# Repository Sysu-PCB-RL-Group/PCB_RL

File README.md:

# PCB_RL

基于强化学习的 PCB 自动布局（Double DQN）。

> ⚠️ 本项目 **2026-09-22 起整体重构**：旧的 5 步动作栈（`env/pcb_layout_env.py` +
> `dqn/` + `config/argument.txt` + `main.py/run.py/run_inference.py` 那套）**已废弃并删除**。
> 本文以下内容全部是现行架构。

## 先读这三份

- **技术总览（新人从这里开始，约 300 行）**：[`docs/项目技术文档.md`](docs/项目技术文档.md)
- **当前参数一览（现在到底配的是什么）**：[`PARAMS.md`](PARAMS.md)
- **设计台账（唯一事实来源，2400+ 行，含每个数字的由来）**：[`docs/导入信息重构.md`](docs/导入信息重构.md)

（重构前的旧文档在 `docs/旧版结构文档/`，**已作废**，仅作历史对照。）

## 环境要求

| 项 | 要求 | 说明 |
|---|---|---|
| Python | **3.11** | 项目既有环境即 3.11（conda 环境名 `pcb_rl_311`）；更低版本未验证 |
| 第三方依赖 | 只有 5 个 | `numpy` / `matplotlib` / `gymnasium` / `torch` / `pytest`，见 `requirements.txt`（实测全仓库只 import 这 5 个） |
| KiCad | **训练/推理都不需要** | 只有「重建缓存」和「读真实板的测试」需要 KiCad 10.0+，见下文 |
| 图形显示 | **不需要** | 3 个绘图模块都强制了 `matplotlib.use("Agg")`，没有 `DISPLAY` 也能出图 |
| 网络 | 只有装依赖时需要 | 能访问 PyPI（或内网镜像）即可；依赖装完后训练/推理全程离线 |
| 磁盘 | 约 62 MB | 其中 `data/` 约 62 MB（板源文件 + 离线缓存） |

## 安装（新机器 / Linux 服务器）

```bash
git clone https://github.com/Sysu-PCB-RL-Group/PCB_RL.git
cd PCB_RL

# ① conda（推荐，与本机环境同名同版本）
conda create -n pcb_rl_311 python=3.11 -y
conda activate pcb_rl_311
# ② 或者 venv
#   python3 -m venv .venv && source .venv/bin/activate

python -m pip install --upgrade pip
python -m pip install torch --index-url https://download.pytorch.org/whl/cpu
python -m pip install -r requirements.txt

# 自检：这行必须打印出版本号，否则说明解释器或依赖没装对
python -c "import torch, numpy, gymnasium, matplotlib; print(torch.__version__, numpy.__version__)"
```

想用 GPU：把 torch 那一行换成

```bash
python -m pip install torch --index-url https://download.pytorch.org/whl/cu124
```

训练时再加 `--device cuda`（**默认是 `cpu`**）。

## 最快跑起来

```bash
python main.py train        # 训练：默认 1000 局 → output/
python main.py infer        # 推理：读 output/best.pt → result/
python main.py help         # 用法
python main.py train --help # 训练的全部参数

# 冒烟（几分钟）：装完环境先跑这个，确认跑得通再上正式训练
python main.py train --episodes 5 --eval-every-episodes 5 --log-every 1 --out output_smoke

python -m pytest tests -q   # 测试（需要 KiCad 的用例会自动 skip）
```

`main.py train|infer` 的参数**原样透传**给 `scripts/train_dqn.py` /
`scripts/infer_dqn.py`，所以用 `--help` 看全部选项。

Windows 本机等价写法（本机 conda 环境的绝对路径）：

```powershell
cd E:\PCB_AI\PCB_RL
& E:\miniconda\envs\pcb_rl_311\python.exe main.py train
```

## 常用参数

默认值来自 `scripts/train_dqn.py`：

| 参数 | 默认值 | 用途 |
|---|---|---|
| `--episodes` | `1000` | 训练局数（冒烟用 `5`） |
| `--device` | `cpu` | `cpu` / `cuda` |
| `--threads` | `0` | torch CPU 线程数；`0` = 用默认（吃满核，多人共用机器时建议显式限制） |
| `--out` | `output` | 产物目录（**训练开始时会先清空该目录**，见下） |
| `--boards` | 全部 | 逗号分隔的板名，只跑其中几块 |
| `--seed` | `114514` | 随机种子，固定（连网络初始化都由它决定） |
| `--eval-every-episodes` | `50` | 每多少局评估一次（评估更优就写 `best.pt`） |

## 输入数据与产物

- **输入**：`data/model_cache/` —— 16 块板的离线几何缓存（`index.json` + 16 个
  `.pkl`，共 17 个文件、约 1.1 MB，**随仓库一起 clone 下来**）。这是训练/推理
  **唯一**的几何来源：**不要删、也不要重新生成**（重新生成需要 KiCad）。
- **产物**：`output/`（`best.pt` / `train_curves.png` / `train.log` / `log.jsonl`）、
  `result/`。这两类目录都在 `.gitignore` 里，不会污染仓库。
- ⚠️ **`--out` 指向的目录会在训练开始时被清空**。代码里有安全闸：目标目录若含
  `.git` / `data` / `env` / `tests` / `scripts` / `docs` / `utils` 之一（或就是仓库
  根目录）会直接报错拒绝执行 —— 但别去试。

## 关于 KiCad

训练与推理**不需要 KiCad**：`env/` 里 0 处调用 `pcbnew`（只在一条注释里提到），
几何全部从 `data/model_cache/` 读。只有下面两件事需要本机装 KiCad **10.0+**
并设置 `KICAD_PATH`：

1. 重建模型缓存：`python scripts/dump_models.py`
2. 读真实板的测试：`pytest tests/kicad`

没装 KiCad 时，`pytest tests` 里需要 KiCad 的用例会**自动跳过**，其余照常运行。

下载：<https://www.kicad.org/download/>

## 训练要多久 / 怎么盯进度

默认 1000 局（16 块板），**本机 CPU 实测参考约 4.4 小时**。训练过程中每 10 局往
`output/train.log` 打一行进度、每 50 局打一行评估；日志每局都落盘，可以随时

```bash
tail -f output/train.log
```

看进度。

## 排障

| 症状 | 原因 / 处理 |
|---|---|
| `main.py` 提示"这个解释器没有 torch" | 用错解释器了：必须用装了依赖的那个（见「安装」） |
| `CacheError: 缓存索引不存在：…` | `data/model_cache/index.json` 缺失 —— 从仓库重新 clone，别删缓存 |
| `CacheVersionError` | 缓存版本与代码不匹配：代码改过 `PcbModel` 字段，需要重新 dump（要有 KiCad） |
| 训练一开始就报"拒绝清零 …" | `--out` 指到了仓库目录，换成 `output` 之类的独立目录 |
| 出图里的中文显示成方框 | 运行环境缺中文字体。仓库里有 `setup_chinese_font` 做回退（`utils/viz_layout.py`），但**未在没装字体的 Linux 上验证过**；只影响图面文字，不影响数值与训练结果 |

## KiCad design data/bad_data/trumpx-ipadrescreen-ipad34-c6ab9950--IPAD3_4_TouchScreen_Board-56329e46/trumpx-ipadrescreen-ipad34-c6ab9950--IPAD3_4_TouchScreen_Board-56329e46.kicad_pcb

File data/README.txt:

此目录存放 PCB RL 项目的训练/推理数据与生成产物。

## 目录结构
- kicad-native-batch/   立创 EDA 导出的真实 KiCad 项目（.kicad_pcb），供训练循环扫描。
                        env/pcb_layout_env.py 的 get_all_files() 会递归扫描此目录。
- expert_transitions/   专家轨迹生成产物：
                          * <board>_expert.json     量化后的 transition 缓存（训练注入用）
                          * <board>_expert_raw.json  raw 轨迹缓存（含 shift / base / 变异类型 /
                                                    拆分前完整 reward，供 analyze_expert.py 审查）
- README.txt / .gitkeep 本说明与空目录占位文件。

## 当前状态（2026-08-24）
- 唯一训练板：开关小板
  （ran-pang-airlink-86231b34--开关小板-883285b3，FP=6, Net=3, grid 36×36）。
- 自 2026-08-01 起统一使用真实 KiCad 数据，不再用 env/mock_pcb.py 合成数据。
- 专家轨迹生成：python generate_expert_only.py --board 开关小板
- 轨迹质量审查：python analyze_expert.py --board airlink

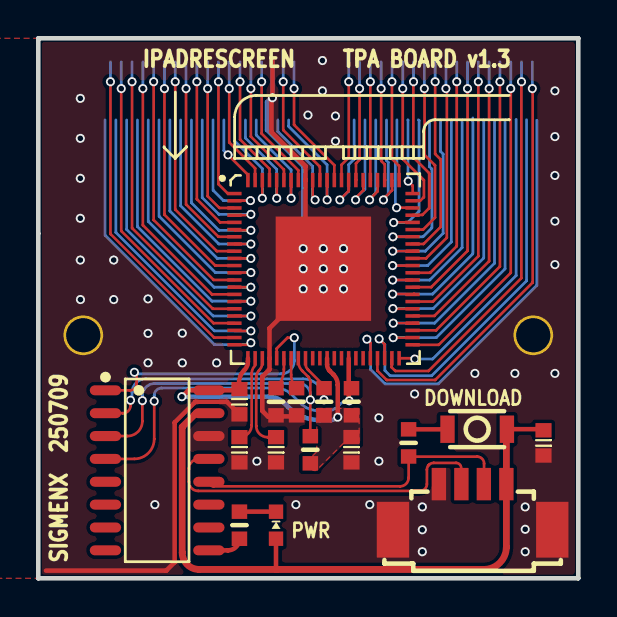
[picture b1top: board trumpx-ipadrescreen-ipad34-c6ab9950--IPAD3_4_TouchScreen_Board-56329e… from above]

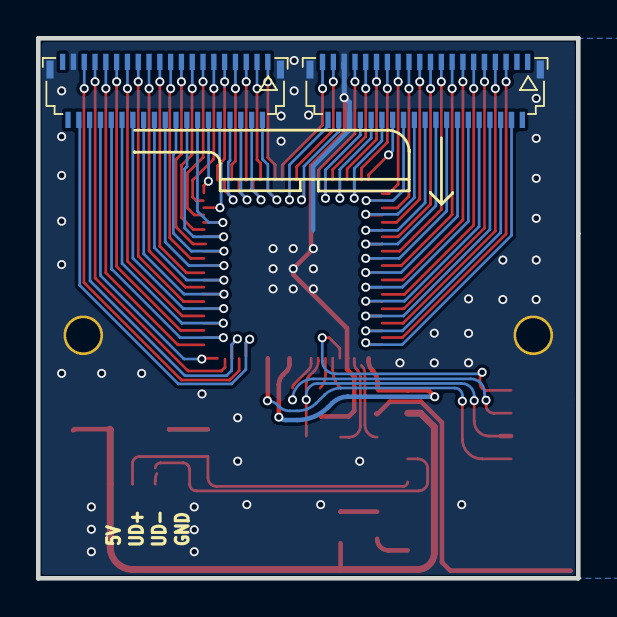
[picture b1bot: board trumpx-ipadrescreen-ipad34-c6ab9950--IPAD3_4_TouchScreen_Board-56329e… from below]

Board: 2 copper layers, 30.0 x 30.0 mm, 19 parts (2 on the bottom side), 86 nets.

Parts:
C1, C2, C3, C5, C6: c0603_neo
FPC2: CONN-SMD_1.25-4PWB
LED1: LED0603
R1, R2, R3, R4, R5, R6, R7: r0603_neo
U1: GT9110
U2, U3: CONN-SMD_FH26-39S-0.3SHW
U4: SW-SMD_L3.0-W2.0-LS3.5
U5: SOP-16_L10.0-W3.9-P1.27-LS6.0-BL

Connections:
$1N6411: C2.2, U1.24
$1N6412: C3.2, U1.25
$1N6447: R1.2, U4.1
$1N6516: R7.2, U5.9
$1N6523: LED1.2, R7.1
+5V: C5.2, FPC2.4, LED1.1, U4.2, U5.15
GND: C1.1, C2.1, C3.1, C5.1, C6.1, FPC2.1, FPC2.5, FPC2.6, R5.2, R6.2, U1.26, U1.80, U1.89, U2.37, U2.40, U2.41, U3.34, U3.35, U3.40, U3.41, U5.14
INT: U1.27, U5.1
MT_IN0: U1.22, U3.4
MT_IN1: U1.21, U3.5
MT_IN2: U1.20, U3.6
MT_IN3: U1.19, U3.7
MT_IN4: U1.18, U3.8
MT_IN5: U1.17, U3.9
MT_IN6: U1.16, U3.10
MT_IN7: U1.15, U3.11
MT_IN8: U1.14, U3.12
MT_IN9: U1.13, U3.13
MT_IN10: U1.12, U3.14
MT_IN11: U1.11, U3.15
MT_IN12: U1.10, U3.16
MT_IN13: U1.9, U3.17
MT_IN14: U1.8, U3.18
MT_IN15: U1.7, U3.19
MT_IN16: U1.6, U3.20
MT_IN17: U1.5, U3.21
MT_IN18: U1.4, U3.22
MT_IN19: U1.3, U3.23
MT_IN20: U1.2, U3.24
MT_IN21: U1.1, U3.25
MT_IN22: U1.88, U3.26
MT_IN23: U1.87, U3.27
MT_IN24: U1.86, U3.28
MT_IN25: U1.85, U3.29
MT_IN26: U1.84, U3.30
MT_IN27: U1.83, U3.31
MT_IN28: U1.82, U3.32
MT_IN29: U1.81, U3.33
MT_OUT0: U1.40, U2.36
MT_OUT1: U1.41, U2.35
MT_OUT2: U1.42, U2.34
MT_OUT3: U1.43, U2.33
MT_OUT4: U1.44, U2.32
MT_OUT5: U1.45, U2.31
MT_OUT6: U1.46, U2.30
MT_OUT7: U1.47, U2.29
MT_OUT8: U1.48, U2.28
MT_OUT9: U1.49, U2.27
MT_OUT10: U1.50, U2.26
MT_OUT11: U1.51, U2.25
MT_OUT12: U1.52, U2.24
MT_OUT13: U1.53, U2.23
MT_OUT14: U1.54, U2.22
MT_OUT15: U1.55, U2.21
MT_OUT16: U1.56, U2.20
MT_OUT17: U1.57, U2.19
MT_OUT18: U1.58, U2.18
MT_OUT19: U1.59, U2.17
MT_OUT20: U1.60, U2.16
MT_OUT21: U1.61, U2.15
MT_OUT22: U1.62, U2.14
MT_OUT23: U1.63, U2.13
MT_OUT24: U1.66, U2.12
MT_OUT25: U1.65, U2.11
MT_OUT26: U1.64, U2.10
MT_OUT27: U1.67, U2.9
MT_OUT28: U1.68, U2.8
MT_OUT29: U1.69, U2.7
MT_OUT30: U1.70, U2.6
MT_OUT31: U1.71, U2.5
MT_OUT32: U1.72, U2.4
MT_OUT33: U1.73, U2.3
MT_OUT34: U1.74, U2.2
MT_OUT35: U1.75, U2.1
MT_OUT36: U1.76, U3.39
MT_OUT37: U1.77, U3.38
MT_OUT38: U1.78, U3.37
MT_OUT39: U1.79, U3.36
OPT1: R5.1, U1.28
OPT2: R6.1, U1.29
RST-TS: R4.2, U1.37, U5.4
SCL: R3.1, U1.31, U5.2
SDA: R2.1, U1.30, U5.3
UD+: FPC2.3, R1.1, U5.12
UD-: FPC2.2, U5.13
VDD33: C1.2, C6.2, R2.2, R3.2, R4.1, U1.23, U1.34, U5.16

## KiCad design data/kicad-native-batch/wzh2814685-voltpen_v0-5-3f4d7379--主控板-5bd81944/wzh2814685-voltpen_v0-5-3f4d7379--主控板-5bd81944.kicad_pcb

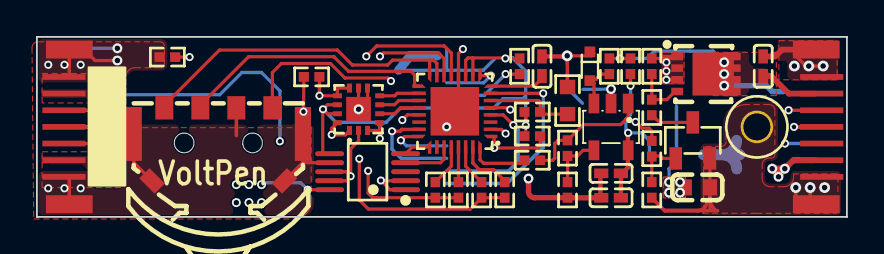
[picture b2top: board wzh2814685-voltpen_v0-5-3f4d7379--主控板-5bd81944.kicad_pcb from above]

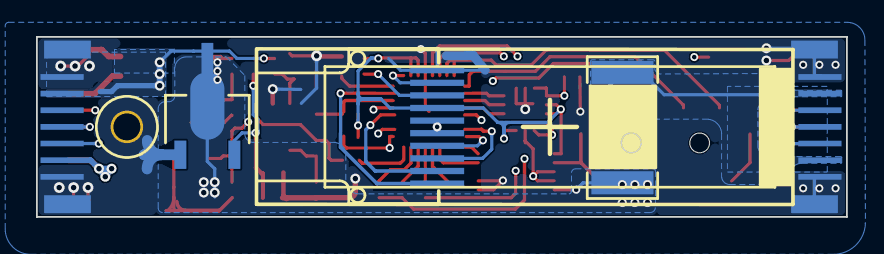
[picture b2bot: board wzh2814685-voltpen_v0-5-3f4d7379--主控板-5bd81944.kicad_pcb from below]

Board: 4 copper layers, 45.0 x 10.0 mm, 37 parts (3 on the bottom side), 39 nets.

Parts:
C1: C0603
C2, C3, C4, C5: C0402
D1: SOD-523_L1.2-W0.8-LS1.6-FD
Q1: WDFN-8_L3.3-W3.3-P0.65-BL
Q2: SOT-23-3_L2.9-W1.3-P1.90-LS2.4-BR
R1, R2, R3, R4, R5, R6, R7, R8, R9, R10, R11, R12, R13, R14, R15, R16, R17, R18: R0402
R19: R2512
RT1: R0603
SW1: SW-SMD_TM-2023-1
TFT-1: 0.99寸-GC9D01N
U1: QFN-32_L4.0-W4.0-P0.40-TL-EP2.7-1
U2: SOT-23-5_L3.0-W1.7-P0.95-LS2.8-BR
U3: MLP-14_L2.5-W2.5-P0.50-BL-EP
U4: MSOP-10_L3.0-W3.0-P0.50-LS5.0-BL
U5: SOT-89-3_L4.5-W2.5-P1.50-LS4.2-BR
USB1, USB2: TYPE-C 14P母座

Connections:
3.3V: C2.1, C4.2, R1.2, R2.2, R10.1, R15.2, TFT-1.7, U1.10, U1.11, U2.5, U3.3, U3.4, U3.12, U3.13, U4.6, U5.3
$1N32: R2.1, TFT-1.8
$1N39: C3.2, U1.8
$1N64: R5.2, R6.1, U2.1
$1N65: R4.2, R5.1, U2.4
$1N66: D1.2, R3.2, U2.3
$1N74: Q2.1, R7.2, R16.2
$1N893: Q2.3, R8.1
$1N902: Q1.4, R8.2, R9.2
ADCN: R1.1, RT1.1, U1.6
ADC_IRON: R6.2, U1.32
BK: TFT-1.9, U1.9
CC1: R17.1, U3.10, U3.11, USB1.A5
CC2: R18.1, U3.1, U3.14, USB1.B5
D+: R13.1, R14.2, U1.14, USB1.A6, USB1.B6
D-: R11.1, R12.2, U1.13, USB1.A7, USB1.B7
D/C: TFT-1.3, U1.23
DD+: R14.1, U1.29
DD-: R12.1, U1.30
GND: C1.2, C2.2, C3.1, C4.1, C5.1, D1.1, Q2.2, R4.1, R16.1, R17.2, R18.2, RT1.2, SW1.3, SW1.4, SW1.5, SW1.6, SW1.C, TFT-1.5, TFT-1.6, TFT-1.10, U1.12, U1.33, U2.2, U3.8, U3.9, U3.15, U4.1, U4.2, U4.7, U5.1, USB1.A1, USB1.A12, USB1.B1, USB1.B12, USB1.SH, USB2.A1, USB2.A12, USB2.B1, USB2.B12, USB2.SH
H_ID: R15.1, U1.1, USB2.A6, USB2.B6
INT302: U1.20, U3.5
K1: SW1.T, U1.17
K2: SW1.2, U1.15, U1.16
K3: SW1.1, U1.21
PWM: R7.1, U1.5
RES: TFT-1.4, U1.24
SCL: TFT-1.2, U1.4
SCL226: U1.25, U4.5
SCL302: U1.19, U3.6
SDA: TFT-1.1, U1.7
SDA226: U1.27, U4.4
SDA302: U1.18, U3.7
SLP: U1.2, USB2.A7, USB2.B7
TEMP: C5.2, Q1.5, R3.1, R10.2, USB2.A4, USB2.A9, USB2.B4, USB2.B9
UD+: R13.2, U1.28
UD-: R11.2, U1.31
VBUS: C1.1, Q1.1, Q1.2, Q1.3, R9.1, R19.2, U4.10, U5.2
VBUS_I: R19.1, U3.2, U4.8, U4.9, USB1.A4, USB1.A9, USB1.B4, USB1.B9

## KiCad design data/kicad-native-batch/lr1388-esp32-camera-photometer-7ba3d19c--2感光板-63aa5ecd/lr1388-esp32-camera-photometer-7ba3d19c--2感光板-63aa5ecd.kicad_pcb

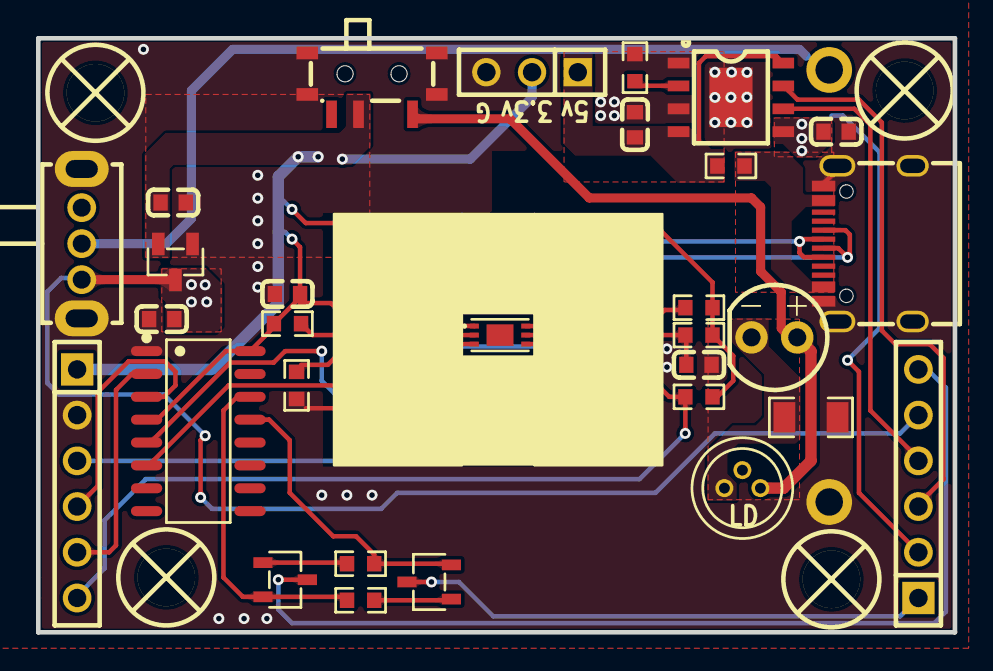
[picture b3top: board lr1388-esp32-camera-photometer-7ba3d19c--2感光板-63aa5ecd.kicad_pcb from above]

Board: 2 copper layers, 50.9 x 33.0 mm, 34 parts (0 on the bottom side), 25 nets.

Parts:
C1, C2, C3, C4, C5, C7: C0603
D1: OPTO-TH_GH05035A2G
H1, H2: HDR-TH_6P-P2.54-V-F
H3: HDR-TH_3P-P2.54-V-F
LED1: LED-TH_BD5.9-P2.54-RD_RED
Q3, Q4: SOT-23-3_L2.9-W1.6-P1.90-LS2.8-BR
R1, R2, R3, R4, R5, R9, R10: R0603
R11: R1206
R12, R13: R0603_2
SCREW1, SCREW2, SCREW3, SCREW4: M3螺丝
SW7: SW-TH_SK12D07VG5
SW8: SW-TH_MSK12C02
U1: WSOF-6_L2.6-W1.6-P0.50-TL-EP
U2: SOT-23-3_L2.9-W1.3-P1.90-LS2.4-BR
U4: ESOP-8_L4.9-W3.9-P1.27-LS6.0-BL-EP
U7: SOP-16_L10.0-W3.9-P1.27-LS6.0-BL
USBC1: USB-C_SMD-TYPE-C-31-M-12

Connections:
$1N1901: R9.2, U4.2
$1N1922: R1.2, R2.2, U1.2
$1N1925: C7.2, R4.1, U1.5
$1N1947: D1.1, LED1.2, SW8.1
$1N1948: D1.3, LED1.1, R11.1
$1N1969: Q4.1, R12.1
$1N1970: Q3.1, R13.1
+3.3V: C1.1, C2.1, H1.1, H3.2, R1.1, R3.2, R4.2, R5.2, SW8.2, U1.1, U2.2, U7.4, U7.16
+5V: C4.2, H3.1, R10.2, U4.4, U4.8
BAT: C5.2, H2.2, SW7.2, U4.5
C_CHARGE: H2.3, U4.7
D+: U7.5, USBC1.A6, USBC1.B6
D-: U7.6, USBC1.A7, USBC1.B7
DTR: Q4.2, R13.2, U7.13
EN: H2.6, Q3.3
GND: C1.2, C2.2, C3.1, C4.1, C5.1, C7.1, H1.2, H3.3, R2.1, R9.1, R11.2, SW7.4, SW7.5, SW8.4, U1.3, U2.1, U4.1, U4.3, U4.9, U7.1, USBC1.0, USBC1.1, USBC1.2, USBC1.3, USBC1.A1, USBC1.A12, USBC1.B1, USBC1.B12
IO0: H2.1, Q4.3
KBAT: C3.2, H2.5, SW7.3, U2.3
RTS: Q3.2, R12.2, U7.14
RXD: H1.5, U7.2
SCL2: H1.3, R3.1, U1.6
SDA2: H1.6, R5.1, U1.4
S_CHARGE: H2.4, U4.6
TXD: H1.4, U7.3
VBUS: R10.1, USBC1.A4, USBC1.A9, USBC1.B4, USBC1.B9

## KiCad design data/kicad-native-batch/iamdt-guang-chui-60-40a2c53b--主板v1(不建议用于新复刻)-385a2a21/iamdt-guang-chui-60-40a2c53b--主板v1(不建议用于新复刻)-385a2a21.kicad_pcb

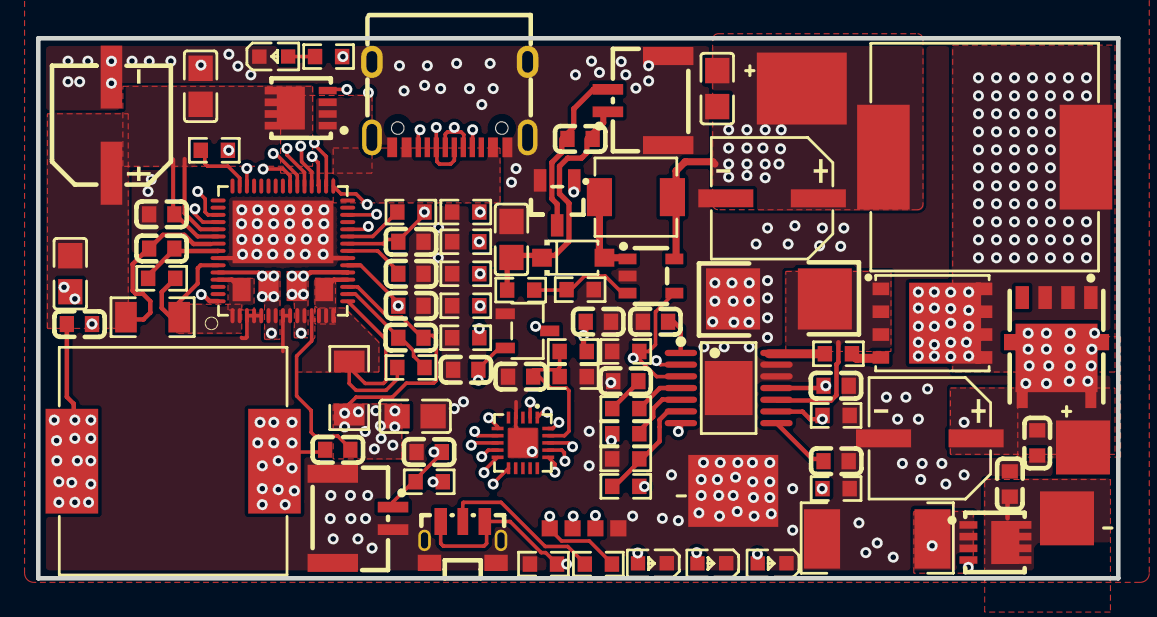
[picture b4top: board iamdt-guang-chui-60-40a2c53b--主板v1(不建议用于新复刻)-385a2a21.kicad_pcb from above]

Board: 4 copper layers, 60.0 x 30.0 mm, 82 parts (0 on the bottom side), 61 nets.

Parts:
C: Test-Point-0.5mm
C1, C15: CAP-SMD_BD6.3-L6.6-W6.6-LS7.0-FD
C3, C4, C5, C6, C8, C16, C17, C18, C19, C20, C21, C22, C23, C24, C26, C27, C28, C29, C30: C0603
C25: CAP-SMD_BD6.3-L6.5-W6.5-LS7.2-FD
CN5, CN6: CONN-TH_2P-P1.25_XUNPU_WAFER-GH1.25-2PLB
CP7, CP8, CP9, CP10, CP11: C0805
D: Test-Point-0.5mm
D1: SOD-123F_L2.7-W1.6-LS3.8-RD-1
G: Test-Point-0.5mm
L1: IND-SMD_L4.4-W4.2
LED1, LED2, LED3, LED4: LED0603-RD_WHITE
Q1, Q3: POWERDI3333-8_DMN7022LFGQ-7
Q4: SOT-23-3_L2.9-W1.5-P1.90-LS2.6-BR
R4, R21: R1206
R5, R6, R7, R8, R11, R12, R13, R20, R26, R27, R28, R29, R30, R31, R32, R33, R34, R72, R74, R75, R76, R77, R78, R79, R80: R0603
RCS1: RES-SMD_L6.4-W3.2-A
Rs1: RES-SMD_L6.4-W3.2-R2512
SW1: SW-TH_SHOU-HAN_TS36XL-3.5
U1: TSSOP-14_L5.0-W4.4-P0.65-LS6.4-BL-EP
U3, U10: IND-SMD_L13.5-W12.8
U4: PG-TDSON-8_L5.9-W5.2-P1.27-LS6.2-BL-EP
U5: SO-8FL_L5.2-W5.8-P1.27-LS6.2-BL-EP
U11: QFN-7*7-60-5
U12: SOT-23-5_L3.0-W1.6-P0.95-LS2.8-BL
U13: QFN-20_L3.0-W3.0-P0.40-BL-EP1.7
U15: SOT-23-3_L2.9-W1.6-P1.90-LS2.8-BR
USB1: USB-C-SMD_TYPE-C-6PIN-2MD-073
V: Test-Point-0.5mm

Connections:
7209DIM: U1.2, U13.2
7209EN: R20.2, U1.3, U12.4, U13.1
$1N264: C3.2, U1.1
$1N387: R5.2, U1.4
$1N564: R7.2, U1.7
$1N2154: R6.1, U1.5
$1N13969: RCS1.2, U1.10, U4.1, U4.2, U4.3
$1N14432: Q1.4, R13.2, U1.9
$1N15489: C5.2, U1.8
$1N15599: C4.2, R5.1
$1N17354: R8.2, U4.4
$1N17355: R8.1, U1.14
$1N20761: R11.1, R12.1, U1.6
$1N28212: Q1.1, Q1.2, Q1.3, R6.2, Rs1.2
$1N29777: U3.2, U4.5, U4.6, U4.7, U4.8, U4.9, U5.1, U5.2, U5.3
$1N32185: U11.37, USB1.4
$1N32191: U11.34, USB1.10
$1N32198: U11.35, USB1.6, USB1.8
$1N32204: U11.36, USB1.5, USB1.7
$1N32461: C18.1, U11.60
$1N32472: C17.1, U11.12
$1N32816: C19.1, R26.1, U11.17
$1N33011: C21.2, U11.23
$1N33016: C22.2, R32.1, R33.1, U11.24
$1N33115: R27.1, U11.26
$1N33198: R28.1, U11.31
$1N33293: R29.1, U11.28
$1N33353: R30.2, U11.32
$1N33459: R31.2, U11.33
$1N33582: R32.2, U11.25
$1N33603: R33.2, U11.44
$1N33920: LED1.2, R72.1
$1N33955: R72.2, U11.43
$1N34076: C23.2, R34.1, U11.53
$1N34291: Q3.4, U11.49
$1N34301: Q3.1, Q3.2, Q3.3, U11.48, USB1.2, USB1.11
$1N34904: C23.1, C24.2, C25.1, CP9.2, CP10.2, Q3.5, R4.2, U11.50, U11.51, U11.52
$1N34934: R21.2, R26.2, U11.13, U11.14, U11.15, U11.16, U11.19, U11.64
$1N34942: C17.2, U10.2, U11.10, U11.11, U11.20, U11.63
$1N34952: R4.1, R34.2, U11.1, U11.2, U11.55, U11.57, U11.61
$1N34960: C18.2, U10.1, U11.6, U11.7, U11.56, U11.62
$1N37163: D1.2, L1.2, U12.1
$1N37271: C30.1, CN6.1, CP11.2, D1.1, R74.2
$1N37490: R74.1, R75.2, U12.3
$1N44107: C26.1, R79.1, U13.6, U15.2, V.1
$1N44580: C29.1, R76.2, R77.1, U13.19
$1N45278: R79.2, SW1.2
$1N45302: R80.1, SW1.1, SW1.3, U13.16
$1N47945: D.1, U13.7
$1N47951: C.1, U13.8
$1N48261: R78.1, U13.17
$1N48268: C28.2, CN5.1, R78.2, U13.18
$1N48317: Q4.1, U13.20
$1N48444: LED2.2, U13.11
$1N48451: LED3.2, U13.10
$1N48458: LED4.2, U13.9
$1N55823: C30.2, CN6.2, Q4.3
GND: C1.2, C3.1, C4.1, C5.1, C6.2, C8.1, C15.2, C16.1, C20.1, C21.1, C22.1, C24.1, C25.2, C26.2, C27.2, C28.1, C29.2, CN5.2, CN5.3, CN5.4, CN6.3, CN6.4, CP7.1, CP8.1, CP9.1, CP10.1, CP11.1, G.1, LED1.1, LED2.1, LED3.1, LED4.1, Q4.2, R7.1, R12.2, R13.1, R20.1, R27.2, R28.2, R29.2, R30.1, R31.1, R75.1, R77.2, R80.2, RCS1.1, Rs1.1, SW1.4, SW1.5, SW1.6, SW1.7, U1.12, U1.13, U1.15, U11.3, U11.4, U11.5, U11.8, U11.9, U11.22, U11.54, U11.65, U12.2, U13.4, U13.21, U15.1, USB1.1, USB1.12, USB1.13, USB1.14
OUT+: C6.1, C8.2, C15.1, R11.2, U1.11, U5.5, U5.6, U5.7, U5.8
OUT-: C16.2, Q1.5
VCC: C1.1, C19.2, C20.2, C27.1, CP7.2, CP8.2, L1.1, R21.1, R76.1, U3.1, U11.18, U11.21, U12.5, U15.3

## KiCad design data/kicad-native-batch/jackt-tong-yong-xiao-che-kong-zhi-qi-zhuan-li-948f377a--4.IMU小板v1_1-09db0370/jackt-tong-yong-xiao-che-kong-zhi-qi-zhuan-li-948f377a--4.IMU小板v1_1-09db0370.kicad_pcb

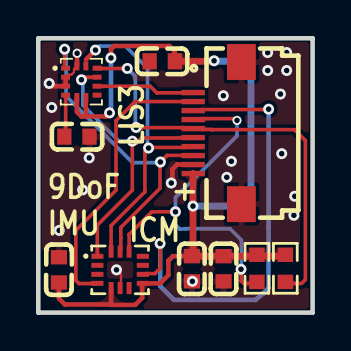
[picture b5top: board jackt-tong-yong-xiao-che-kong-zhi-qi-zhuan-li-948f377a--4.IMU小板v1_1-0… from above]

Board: 2 copper layers, 15.2 x 15.2 mm, 10 parts (0 on the bottom side), 11 nets.

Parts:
C1, C2, C3, C4, C5: C0603
FPC1: FPC-SMD_P0.5-10P_FGS-XJ-H2.0
R1, R2: R0603
U1: LGA-14_L3.0-W2.5-P0.50-TL
U2: LGA-12_L2.0-W2.0-P0.50-BL

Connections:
3V3: C1.2, C2.2, C3.2, C5.2, FPC1.10, R1.2, R2.2, U1.5, U1.8, U2.5, U2.6
$1N533: C4.2, U2.4
GND: C1.1, C2.1, C3.1, C4.1, C5.1, FPC1.9, FPC1.11, FPC1.12, U1.6, U2.2, U2.3, U2.12
ICM_CS: FPC1.4, R1.1, U1.12
ICM_INT: FPC1.2, U1.4
IMU_MISO: FPC1.6, U1.1, U2.9
IMU_MOSI: FPC1.7, U1.14, U2.11
IMU_SCK: FPC1.8, U1.13, U2.1
LIS3_CS: FPC1.5, R2.1, U2.10
LIS3_DRDY: FPC1.1, U2.8
MCO_32K: FPC1.3, U1.9

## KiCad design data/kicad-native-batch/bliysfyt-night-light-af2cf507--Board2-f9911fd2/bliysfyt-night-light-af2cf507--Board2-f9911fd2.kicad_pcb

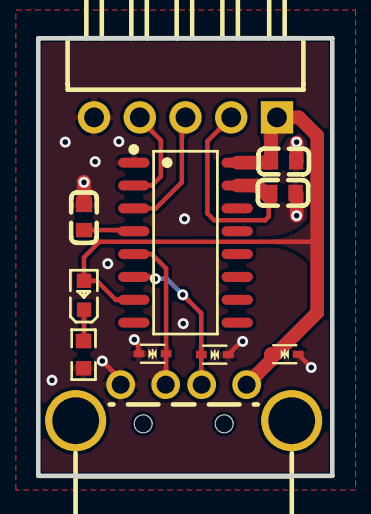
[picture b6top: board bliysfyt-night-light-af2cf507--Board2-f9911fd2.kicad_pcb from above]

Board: 2 copper layers, 16.3 x 24.3 mm, 11 parts (0 on the bottom side), 9 nets.

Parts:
C1, C2, C3: C0603
D2, D3, D4: SOD-523_L1.2-W0.8-LS1.6-BI
H1: HDR-TH_5P-P2.54-H-M-W10.4
LED1: LED0603-RD_RED
R1: R0603
U1: SOP-16_L10.0-W3.9-P1.27-LS6.0-BL
USB1: USB-AM-TH_AM90

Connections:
$1N711: C1.1, U1.4
$1N1523: LED1.1, R1.2
GND: C1.2, C2.1, C3.1, D2.1, D3.2, D4.1, H1.5, R1.1, U1.1, USB1.4
RXD0: H1.4, U1.2
TXD0: H1.3, U1.3
USB2_D+: D4.2, U1.5, USB1.3
USB2_D-: D3.1, U1.6, USB1.2
VCC-3.3V: C3.2, H1.2, U1.15
VIN2: C2.2, D2.2, H1.1, LED1.2, U1.7, U1.16, USB1.1

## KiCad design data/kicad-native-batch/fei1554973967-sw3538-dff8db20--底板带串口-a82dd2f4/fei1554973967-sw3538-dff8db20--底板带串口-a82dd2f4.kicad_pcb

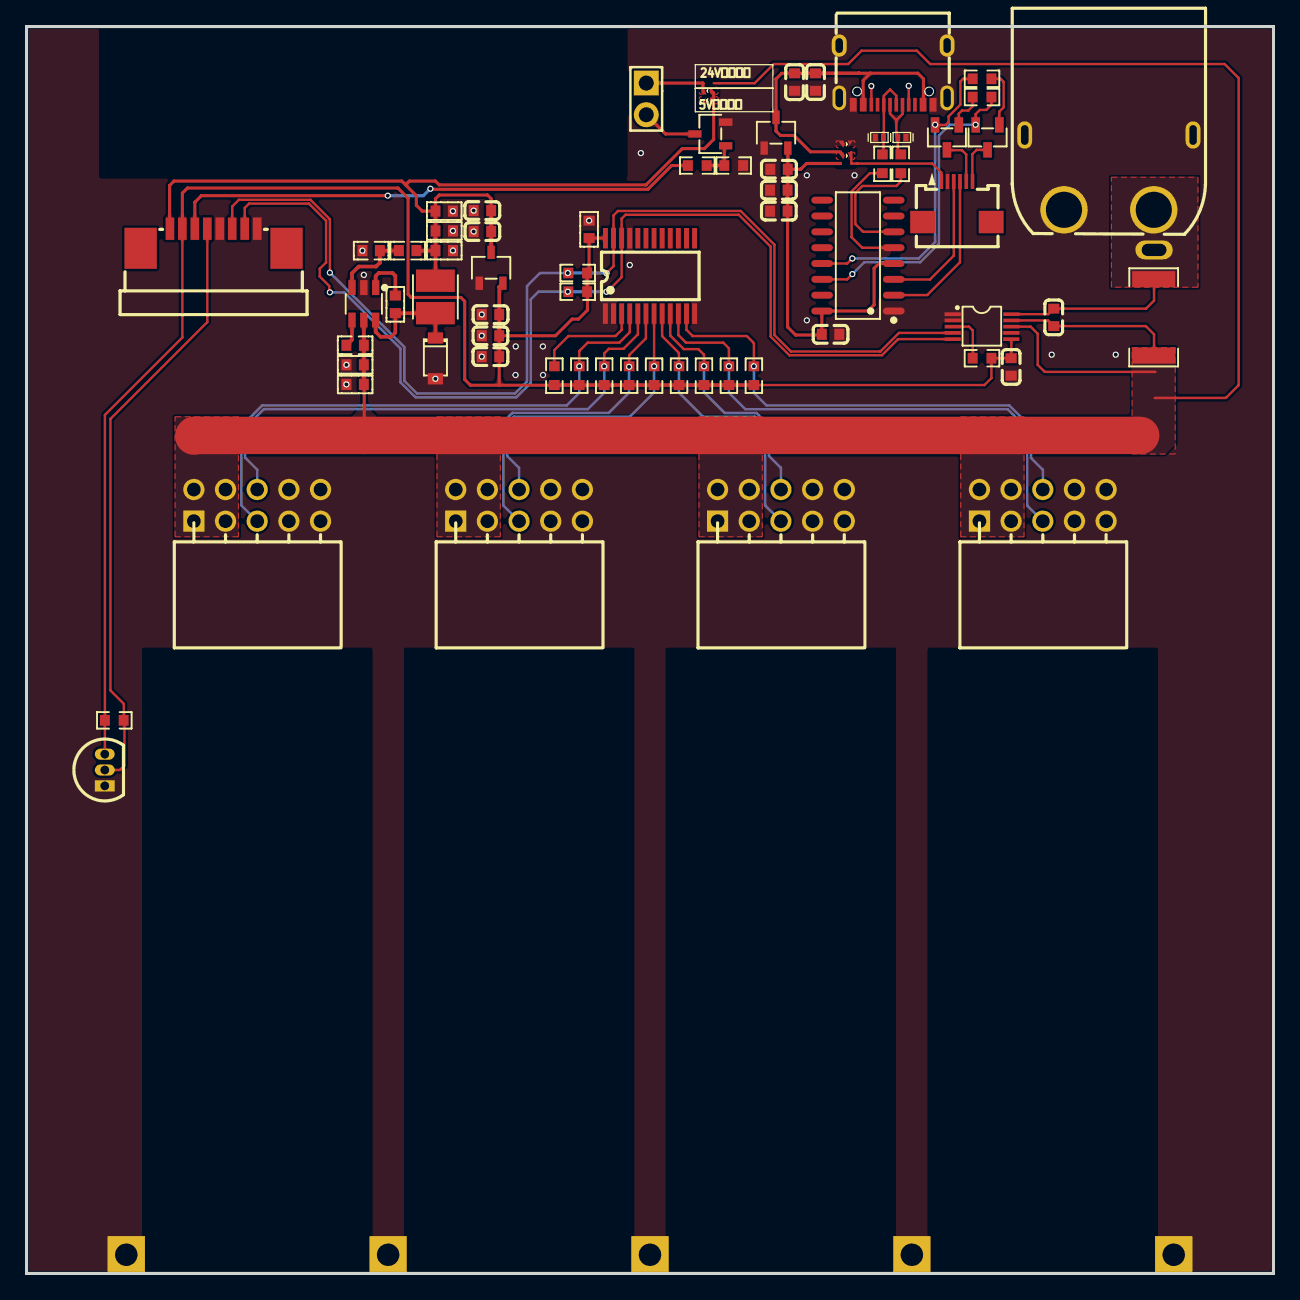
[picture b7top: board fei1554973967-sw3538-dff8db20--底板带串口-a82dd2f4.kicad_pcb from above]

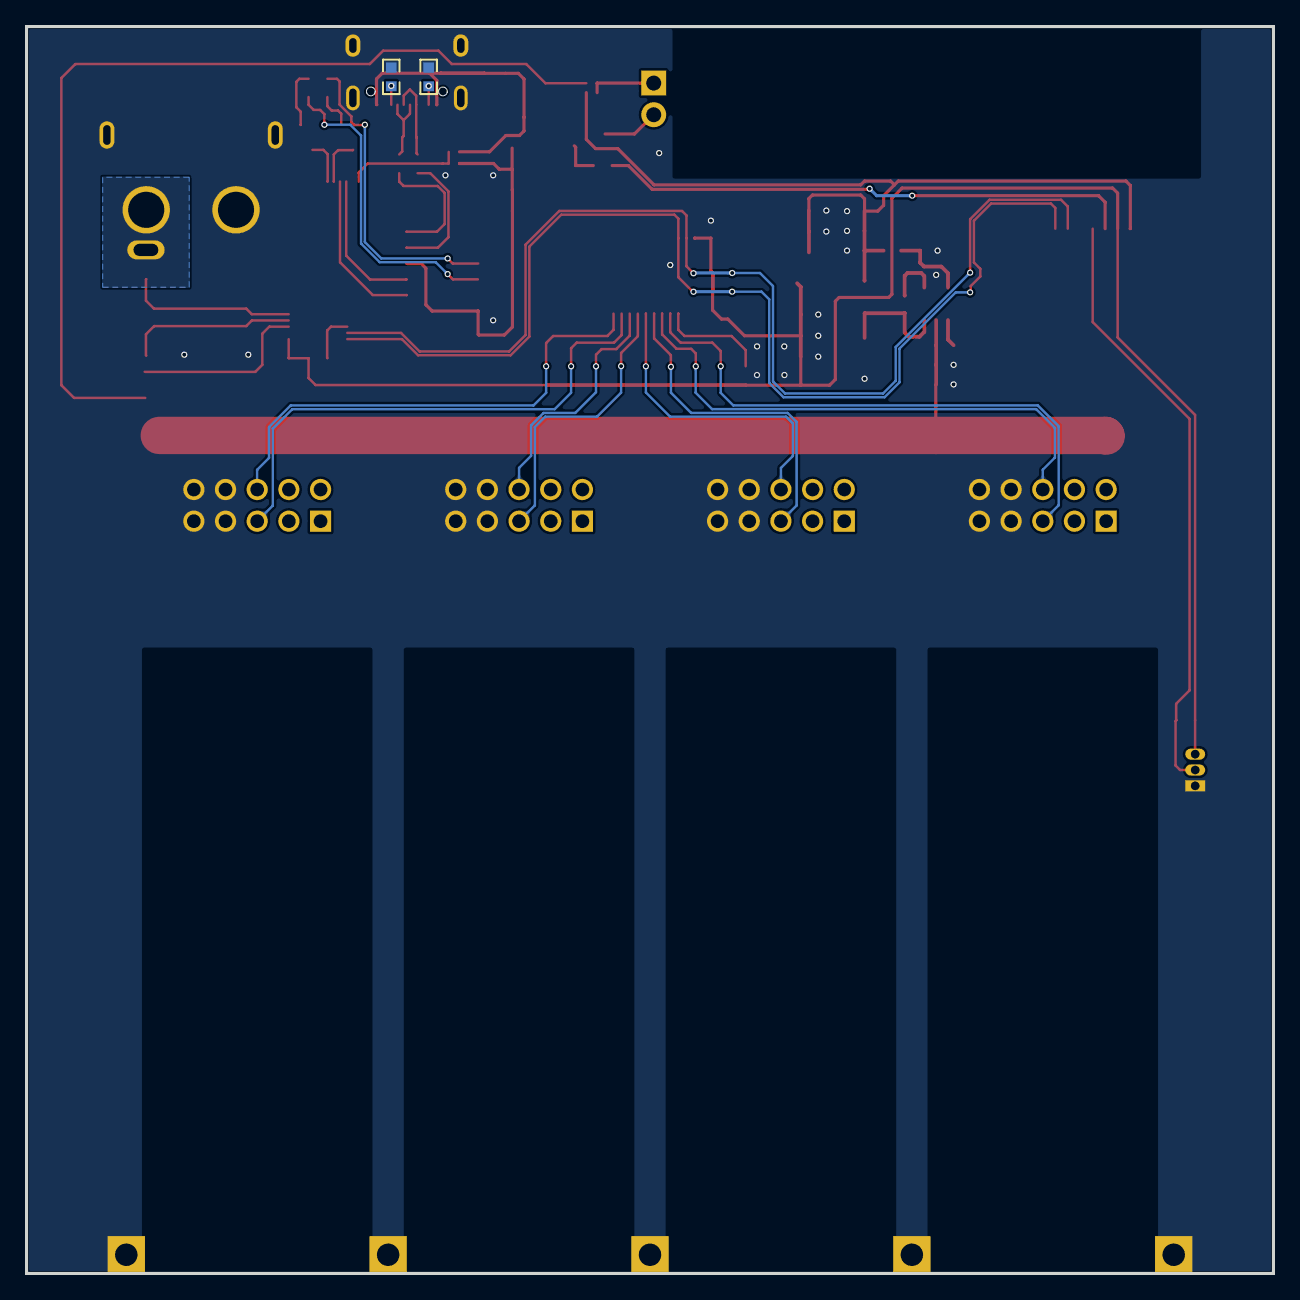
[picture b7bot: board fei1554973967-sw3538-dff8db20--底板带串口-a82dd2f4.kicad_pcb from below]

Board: 2 copper layers, 100.0 x 100.0 mm, 72 parts (2 on the bottom side), 43 nets.

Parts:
+ -: HDR-TH_2P-P2.54-V-M
C1, C2, C4, C13, C17, C18, C19, C69, C70, C72, C73, C85, C89, C90: C0603
C32, C39, C86, C87, C88, C91: c0603
CN1: CONN-TH_XT60PW-M
D1: SOD-123_L2.7-W1.6-LS3.7-RD
D2, D3: DFN1006-BI
FPC1: FPC-SMD_6P-P0.50_SHOU-HAN_0.5-6PQFHY-H1.0
FPC2: FPC-SMD_8P-P1.00_LCS-XJ
H1, H2, H3, H4: HDR-TH_10P-P2.54-H-F-R2-C5-W8.5
L6: IND-SMD_L3.5-W3.0
Q2: SOT-23-3_L2.9-W1.6-P1.90-LS2.8-BL-A
Q4, Q5: SOT-23-3_L2.9-W1.3-P1.90-LS2.4-BR
R1, R2, R3, R4, R5, R6, R7, R8, R9, R10, R11, R35, R36, R37, R38, R39, R40, R43, R44, R45, R46, R47, R48, R49: R0603
R19: R2512
SC29, SC30, SC31, SC32: 短接点0402
U2: TSSOP-24_L7.8-W4.4-P0.65-LS6.4-BL
U10, U20: SOT-23-3_L2.9-W1.6-P1.90-LS2.8-BR
U12: VSSOP-10_L3.0-W3.0-P0.50-LS4.9-BL
U17: SOT-23-6_L2.9-W1.6-P0.95-LS2.8-BL_3
U18: TO-92-3_L4.9-W3.7-P1.27-L
U19: SOP-16_L10.0-W3.9-P1.27-LS6.0-BL
USB1: USB-C-SMD_TYPE-C-6PIN-2MD-073

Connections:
3.3V: C2.2, C4.2, C18.1, C39.1, C86.2, FPC2.7, R1.2, R2.2, R3.2, R4.2, R5.2, R6.2, R7.2, R8.2, R9.2, R10.2, R11.2, R40.1, R43.1, U2.24, U10.2, U12.6, U18.3
3V3: C1.2, C87.2, C90.1, C91.1, SC29.2, U19.4, U19.16, U20.2
24V: C13.2, CN1.2, R19.1, U12.10
$1N2433: R36.2, R37.1, U17.3
$1N2434: C72.1, D1.1, L6.1, U17.6
$1N2440: R35.2, U17.4
$1N2441: C72.2, U17.1
$1N3750: Q2.1, R38.2, R39.2
$1N3873: + -.2, Q2.2
$1N4090: + -.1, SC31.1, SC32.1
$1N6746: R43.2, U12.3
$1N6854: FPC1.1, SC29.1, SC30.1
$1N7284: Q4.1, R46.2
$1N7285: Q5.1, R47.2
$1N7617: R48.2, U19.5
$1N7618: R49.2, U19.6
+5V: C17.1, C19.2, C32.2, C69.2, C70.2, FPC2.8, L6.2, R36.1, SC32.2, U10.3
CC1: R44.2, USB1.4
CC2: R45.2, USB1.10
D+: D2.1, R48.1, USB1.6, USB1.8
D-: D3.2, R49.1, USB1.5, USB1.7
DTR: Q4.2, R47.1, U19.13
EN: FPC1.6, Q5.3
FAN: FPC2.6, R39.1
GND: C1.1, C2.1, C4.1, C17.2, C18.2, C19.1, C32.1, C39.2, C69.1, C70.1, C73.1, C85.1, C86.1, C87.1, C88.1, C89.2, C90.2, C91.2, CN1.1, CN1.3, CN1.4, D1.2, D2.2, D3.1, FPC1.2, FPC2.1, FPC2.4, H1.7, H1.8, H1.9, H1.10, H2.7, H2.8, H2.9, H2.10, H3.7, H3.8, H3.9, H3.10, H4.7, H4.8, H4.9, H4.10, Q2.3, R37.2, R38.1, R44.1, R45.1, U2.1, U2.2, U2.12, U2.21, U10.1, U12.1, U12.2, U12.7, U17.2, U18.1, U19.1, U20.1, USB1.1, USB1.12, USB1.13, USB1.14
GPIO0: FPC1.5, Q4.3
IN: C13.1, C73.2, C85.2, H1.1, H1.2, H1.3, H1.4, H2.1, H2.2, H2.3, H2.4, H3.1, H3.2, H3.3, H3.4, H4.1, H4.2, H4.3, H4.4, R19.2, R35.1, SC31.2, U12.8, U12.9, U17.5
RESET: R5.1, U2.3
RTS: Q5.2, R46.1, U19.14
RX: FPC1.3, U19.3
SCL: FPC2.2, R2.1, U2.22, U12.5
SCL_1: H1.6, R7.1, U2.5
SCL_2: H2.6, R9.1, U2.7
SCL_3: H3.6, R4.1, U2.9
SCL_4: H4.6, R11.1, U2.11
SDA: FPC2.3, R1.1, U2.23, U12.4
SDA_1: H1.5, R6.1, U2.4
SDA_2: H2.5, R8.1, U2.6
SDA_3: H3.5, R10.1, U2.8
SDA_4: H4.5, R3.1, U2.10
TEMP: FPC2.5, R40.2, U18.2
TX: FPC1.4, U19.2
VBUS: C88.2, C89.1, SC30.2, U20.3, USB1.2, USB1.11

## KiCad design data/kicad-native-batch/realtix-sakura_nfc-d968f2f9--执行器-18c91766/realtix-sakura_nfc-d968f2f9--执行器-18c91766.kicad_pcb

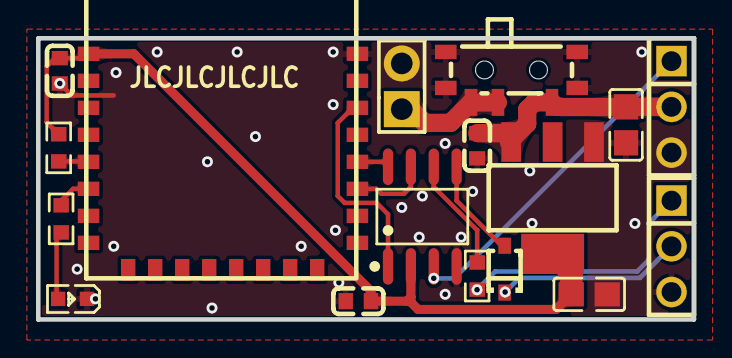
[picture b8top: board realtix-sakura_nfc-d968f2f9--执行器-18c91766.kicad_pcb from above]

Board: 2 copper layers, 36.4 x 15.6 mm, 17 parts (0 on the bottom side), 15 nets.

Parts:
C1, C3, C5: C0603
C2, C4: C0805
D1: SOD-323_L1.6-W1.3-LS2.7-RD
H1: HDR-TH_2P-P2.54-V-M
H2, H3: HDR-TH_3P-P2.54-V-M
LED1: LED0603-RD_RED
R1, R2, R3: R0603
S1: SW-SMD_PCM12SMTR
U1: SOP-8_L5.0-W4.0-P1.27-LS6.0-BL
U2: JDY-25M
U3: SOT_223

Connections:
3V3: C1.2, C4.2, C5.2, R2.2, U1.2, U2.1, U3.4
$1N2476: LED1.2, R3.1
+5V: H1.1, S1.2, S1.3
GND: C1.1, C2.2, C3.2, C4.1, C5.1, H1.2, H2.3, H3.3, LED1.1, S1.4, U1.4, U2.24, U3.1
JDY_IN5: R2.1, U2.5
JDY_PWRC: U1.1, U2.22
JDY_RX: U1.8, U2.20
JDY_STAT: R3.2, U2.6
JDY_TX: U1.7, U2.19
P3.0(RX): D1.2, U1.5
P3.1(TX): R1.1, U1.6
P5.5: H3.1, U1.3
RX: D1.1, H2.2
TX: H2.1, R1.2
VCC: C2.1, C3.1, H3.2, S1.1, U3.3
